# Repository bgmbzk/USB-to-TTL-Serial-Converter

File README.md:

# ⚡ USB-to-TTL Serial UART Converter (Finalized / Tamamlandı)

Bu depo, **CH340G** entegresi ve modern **USB-C** konnektörü temel alınarak tasarlanmış, tam donanımlı bir USB-to-TTL dönüştürücü projesini içerir.

This repository contains the finalized KiCad design files for a professional USB-to-TTL converter based on the **CH340G** IC and a modern **USB-C** connector.

---

## 📸 Proje Görselleri / Project Visuals

### 1. 3D Model Tasarımı / 3D Model Design

*USB-C arayüzü ve CH340G köprüsü ile kompakt ve fiziksel olarak optimize edilmiş nihai tasarım.*

*The final physical layout featuring a compact USB-C interface and the CH340G bridge.*

### 2. Devre Şeması / Schematic Diagram

*Kristal osilatör devresi ve gürültü engelleyici kapasitör katmanlarını içeren hassas elektriksel tasarım.*

*Precise electrical design including the crystal oscillator circuit and decoupling capacitors.*

### 3. PCB Yolları ve Yerleşim / PCB Layout & Routing

*Sinyal bütünlüğü için optimize edilmiş bakır yollar ve geniş yer düzlemi (ground plane) uygulaması.*

*The finalized copper layers with optimized routing and a solid ground plane for signal integrity.*

---

## 🛠️ Teknik Detaylar / Technical Details
- **Main IC:** CH340G (Güvenilir USB-Seri dönüştürücü / Reliable USB-to-Serial bridge)
- **Connector:** USB Type-C (16-pin SMT)
- **Software:** KiCad 8.0
- **Özellikler / Features:** - Optimize edilmiş 12MHz kristal osilatör devresi. / Optimized 12MHz crystal circuit.
    - Profesyonel güç filtreleme kapasitörleri. / Professional-grade power filtering.
    - Kolay prototipleme için net UART çıkış pinleri. / Clear UART breakout pins.

## 📈 Öğrenim Kazanımları / Learning Outcomes
* **Kısıtlamaları Aşmak:** Dar alanlardaki (USB-C) Tasarım Kuralı Hatalarını (DRC) başarıyla çözme yetisi. / Successfully solved DRC violations in tight spaces.
* **Yüksek Yoğunluklu Tasarım:** Sıkışık pin aralıklarında yol yönetimi deneyimi. / Gained experience in high-density trace management.
* **Süreklilik:** Yarım kalan bir projeyi teknik olarak geliştirip üretim aşamasına getirme disiplini. / Demonstrated the ability to push a "stuck" project to completion.

---
*Developed with persistence, curiosity, and a passion for hardware engineering.*

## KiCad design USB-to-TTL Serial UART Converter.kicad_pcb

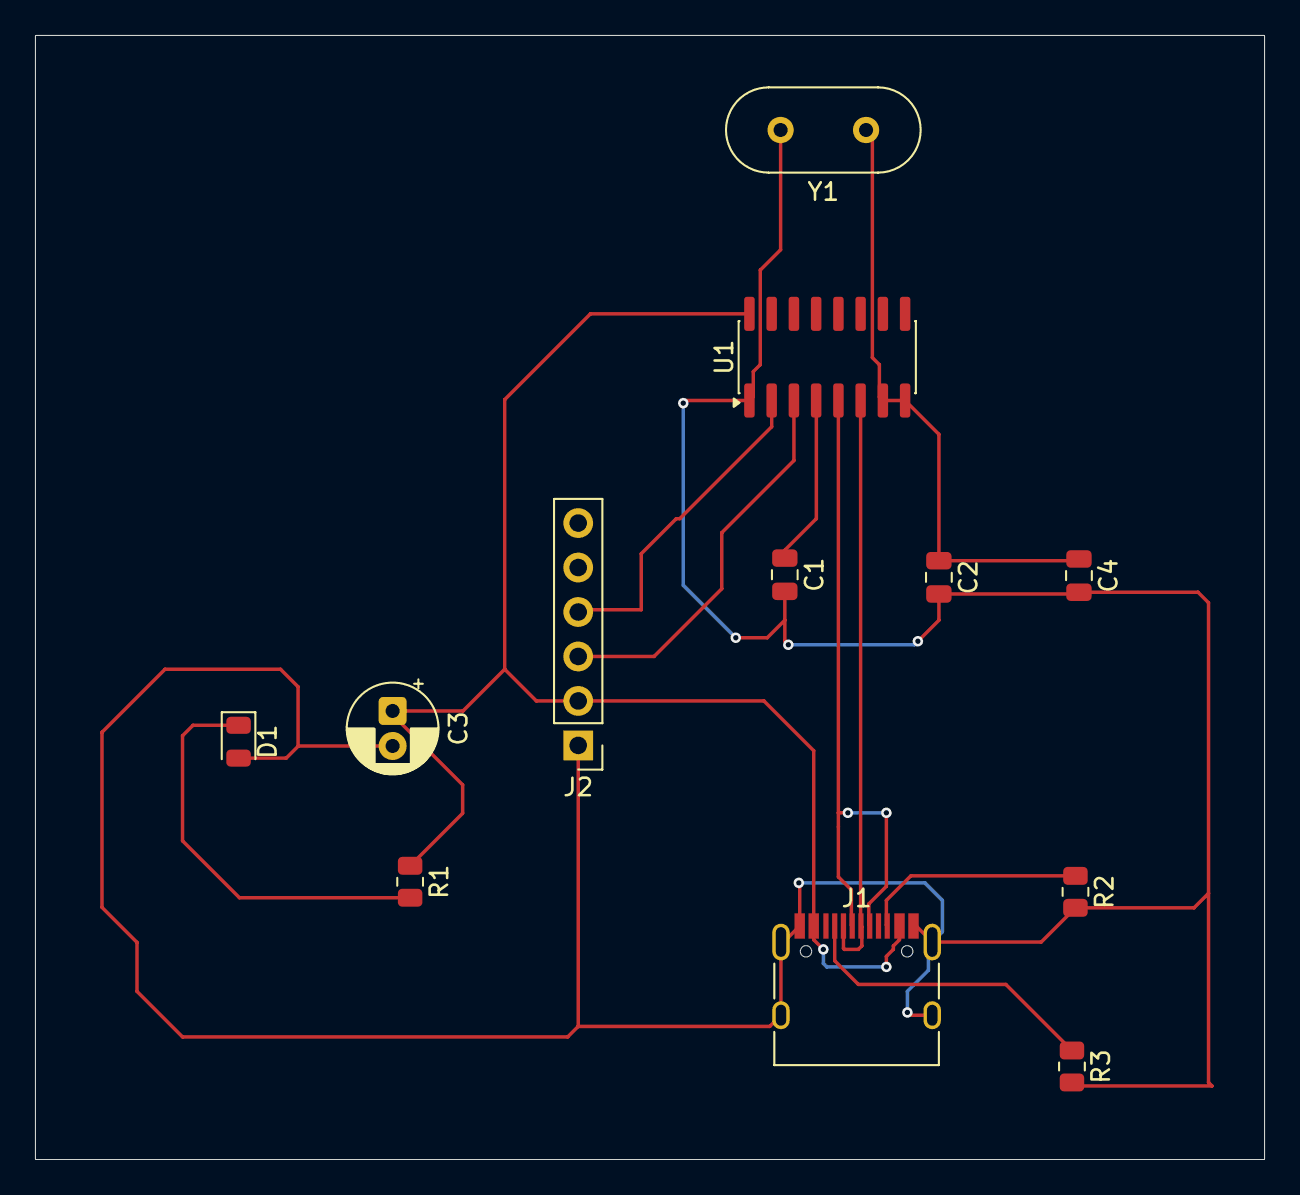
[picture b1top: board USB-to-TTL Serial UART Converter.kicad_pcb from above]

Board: 2 copper layers, 70.2 x 64.2 mm, 12 parts (0 on the bottom side), 11 nets.

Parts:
C1, C2, C4: C; C_0805_2012Metric
C3: C_Polarized_Small_US; CP_Radial_D5.0mm_P2.00mm
D1: LED; LED_0805_2012Metric
J1: USB_C_Receptacle; USB_C_Receptacle_HRO_TYPE-C-31-M-12
J2: Conn_01x06_Pin; PinHeader_1x06_P2.54mm_Vertical
R1, R2, R3: R; R_0805_2012Metric
U1: CH340G; SOIC-16_3.9x9.9mm_P1.27mm
Y1: Crystal_GND2; Crystal_HC49-U_Vertical

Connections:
GND: C1.2, C2.2, C3.2, C4.2, D1.2 (A), J1.A1 (GND), J1.A12 (GND), J1.B1 (GND), J1.B12 (GND), J1.S1 (SHIELD), J2.1, R2.2, R3.2, U1.1 (GND), Y1.2
unnamed: D1.1 (K), R1.2
unnamed: J1.A5 (CC1), R3.1
unnamed: J1.B5 (CC2), R2.1
unnamed: C3.1, J1.A4 (VBUS), J1.A9 (VBUS), J1.B4 (VBUS), J1.B9 (VBUS), J2.2, R1.1, U1.16 (VCC)
unnamed: J2.3, U1.3 (RXD)
unnamed: J2.4, U1.2 (TXD)
unnamed: J1.A6 (D+), J1.B6 (D+), U1.5 (UD+)
unnamed: J1.A7 (D-), J1.B7 (D-), U1.6 (UD-)
unnamed: C1.1, U1.4 (V3)
unnamed: C2.1, C4.1, U1.7 (XI), U1.8 (XO), Y1.1

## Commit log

2026-04-01 Experimental
    This is an experimental layout design. The project is currently on hold due to routing constraints between the USB-C (16-pin) connector and the CH340G IC. It serves as a study of component placement 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
2026-04-05 Revise README for finalized project and translations
    Updated the README to reflect the finalized project status and added Turkish translations for key sections.
2026-04-05 Update README with project visuals and descriptions
    Added project visuals and descriptions in Turkish and English.
